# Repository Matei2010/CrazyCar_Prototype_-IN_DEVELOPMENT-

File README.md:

CrazyCar

This is my project for the Crazy Car Competition at FH JOANNEUM in Graz.

The goal is to design and build a small autonomous racing car. The car is supposed to drive around a track on its own using distance sensors and a custom control system.

I made it because i want to win at the Crazy car competition and beacuse i love it to design complicated PCBs.

Full Assembly:

Hardware

The current design includes five VL53L0X time-of-flight distance sensors at the front of the car. Since these sensors use the same I2C address, an I2C multiplexer is included in the design.

For the motors, I am planning to use RZ7889 motor drivers in combination with TMCS1100A3QDR current sensing. The motors are not fully decided yet. Possible options are high-power N20 geared motors or custom geared coreless motors.At the moment i am leaning more towards n20 Motors.

The car is also planned to have a centrifugal fan underneath it to create suction and increase grip. It will generate about 1-1.5 Kg of downforce on the car. 

PCB

The schematic and PCB layout were designed in KiCad. The current design is waiting for approval from my teacher, since this is my first actual complicated PCB, i like to be sure bevore I waiste money on it.

No PCB has been manufactured yet, and no hardware has been assembled or tested. Some component choices and parts of the design may still change.

Front copper:

Back Copper:

3D_Model:

Schematic:

Repository

This repository contains the KiCad project files, including the schematic and PCB layout.

The project is still in the design phase, so things may change as development continues.

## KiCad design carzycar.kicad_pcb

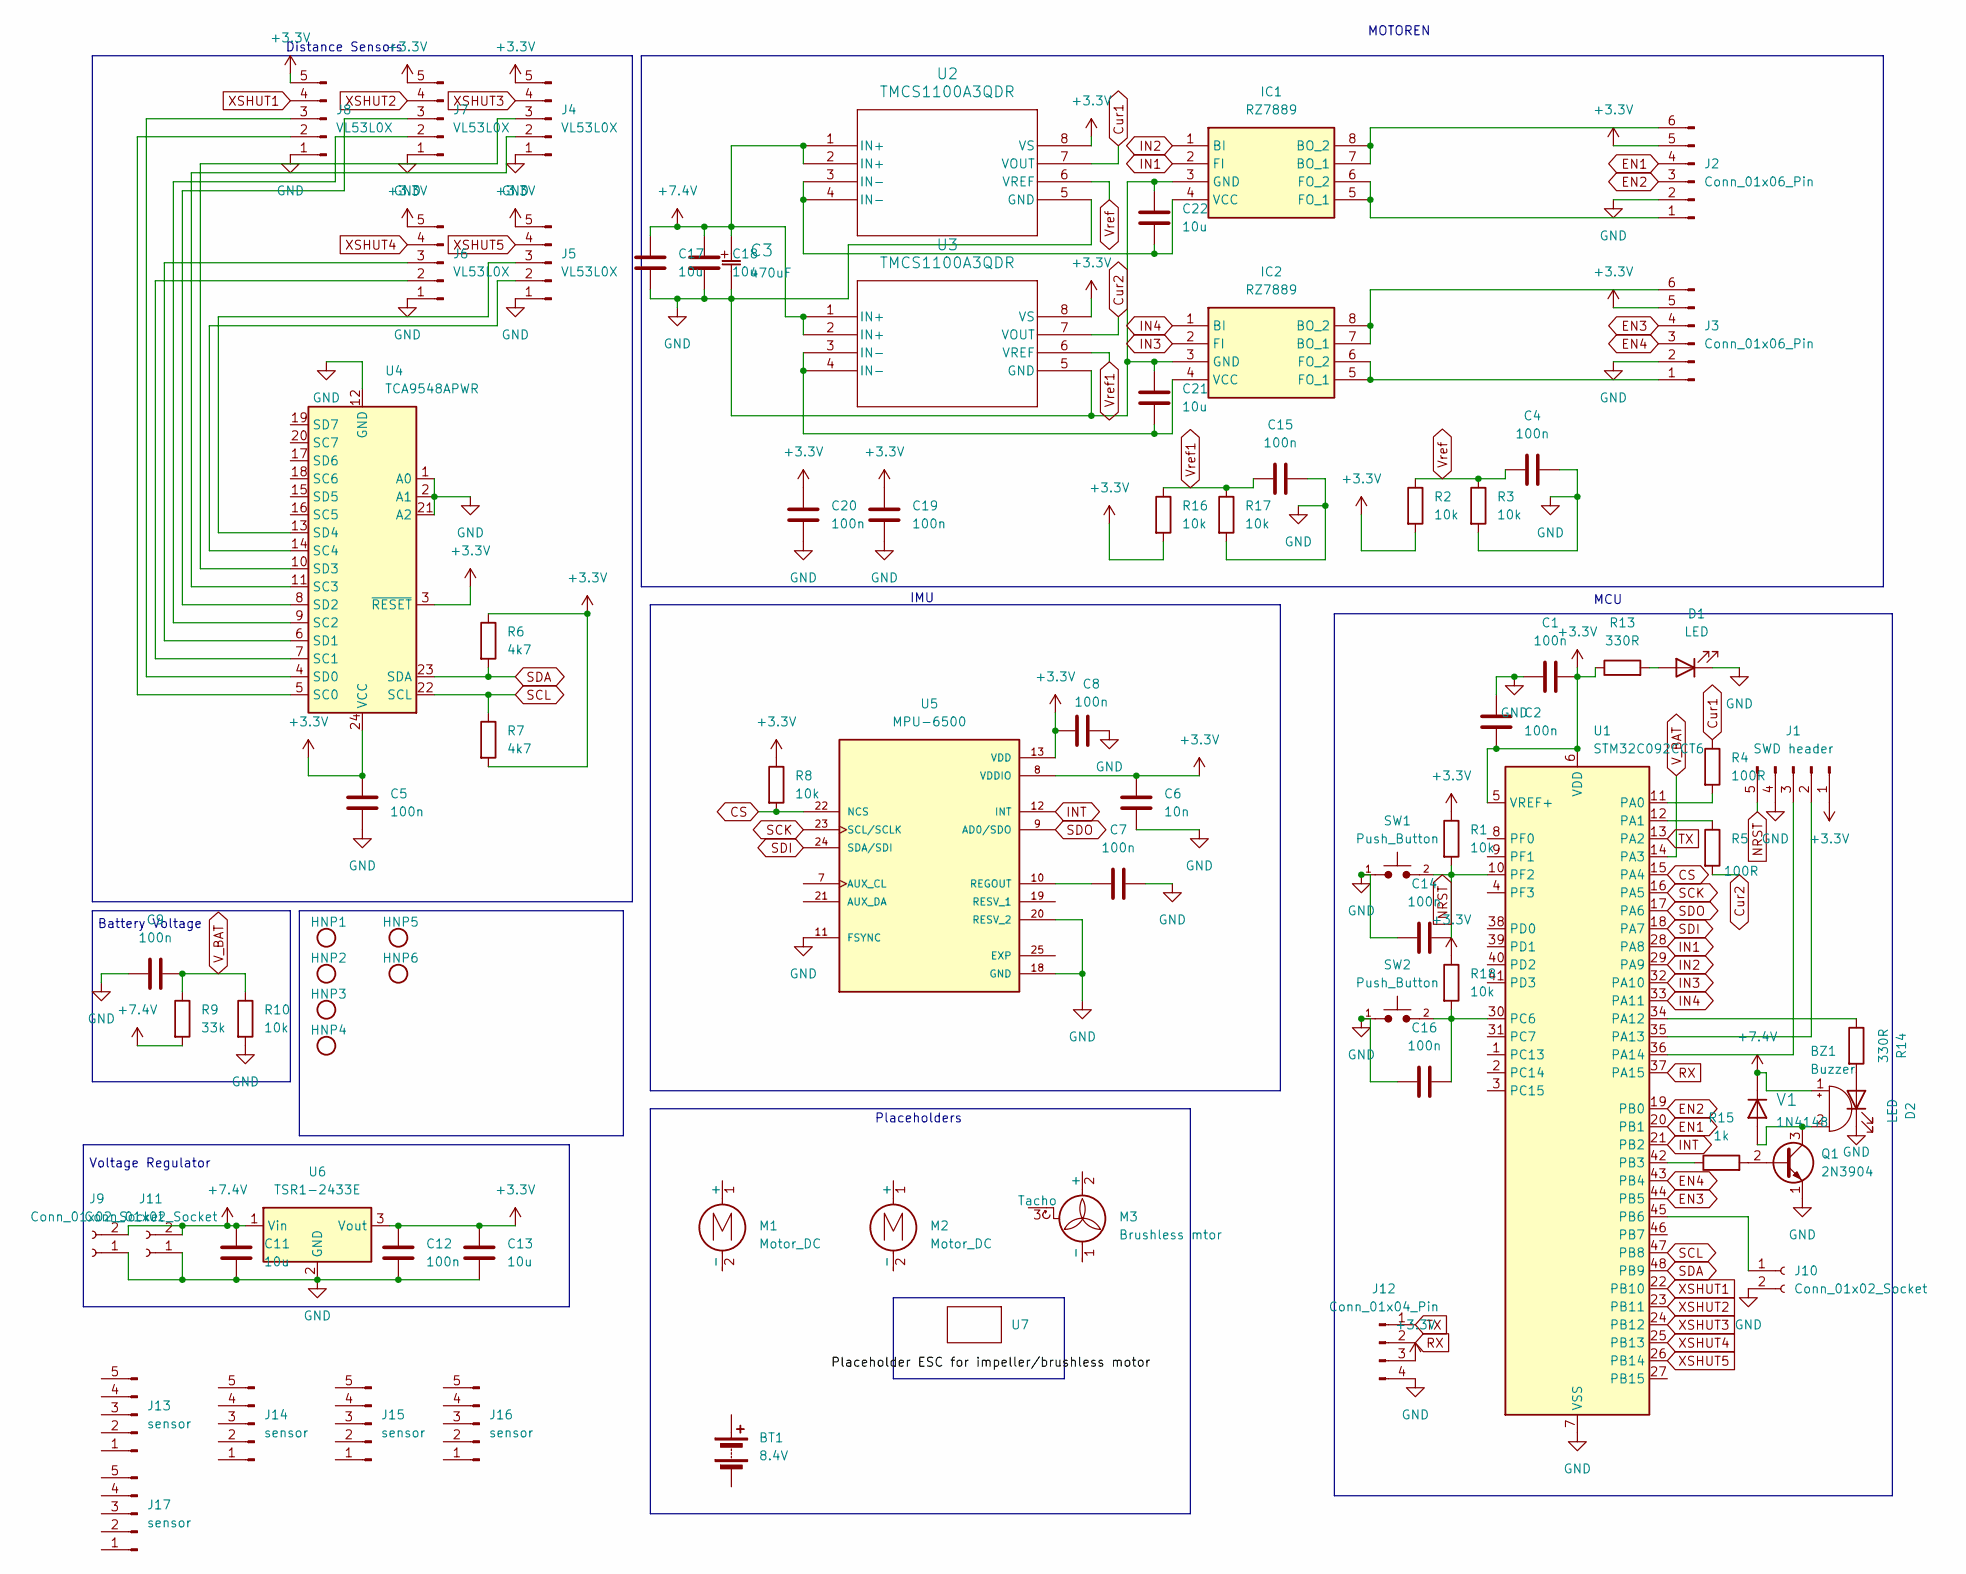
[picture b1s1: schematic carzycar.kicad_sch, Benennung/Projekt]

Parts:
BT1: 8.4V
BZ1: Buzzer; Buzzer_12x9.5RM7.6; PART_NO TMB12A12
C1, C2, C4, C5, C7, C8, C9, C12, C14, C15, C16, C19, C20: 100n; C_0805_2012Metric; PART_NO CC0805KRX7R9BB104
C3: 470uF; CP_Radial_D8.0mm_P3.50mm; PART_NO 03EC0575
C6: 10n; C_0805_2012Metric; PART_NO TCC0805X7R103K500DT
C11, C13, C17, C18, C21, C22: 10u; C_0805_2012Metric; PART_NO GRM21BR61H106KE43L
D1, D2: LED; LED_0805_2012Metric; PART_NO XL-1608SURC-06
HNP1, HNP2, HNP3, HNP4, HNP5, HNP6: NPH; MountingHole_2.2mm_M2
IC1, IC2: RZ7889; SOIC127P600X175-8N; Manufacturer_Part_Number RZ7889
J1: SWD header; PinHeader_1x05_P2.54mm_Vertical; PART_NO B-2100S40P-A110
J2, J3: Conn_01x06_Pin; PinHeader_1x06_P2.54mm_Vertical; PART_NO B-2100S40P-A110
J4, J5, J6, J7, J8: VL53L0X; PinHeader_1x05_P2.54mm_Vertical; PART_NO B-2100S40P-A110
J9, J11: Conn_01x02_Socket; AMASS_XT30U-F_1x02_P5.0mm_Vertical; PART_NO XT30U-F
J10: Conn_01x02_Socket; PinHeader_1x02_P2.54mm_Vertical; PART_NO B-2100S40P-A110
J12: Conn_01x04_Pin; PinHeader_1x04_P2.54mm_Vertical; PART_NO B-2100S40P-A110
J13, J14, J15, J16, J17: sensor
M1, M2: Motor_DC; N20_with_encoder
M3: Brushless mtor
Q1: 2N3904; TO-92_Inline; PART_NO 2N3904BU
R1, R2, R3, R8, R10, R16, R17, R18: 10k; R_0805_2012Metric; PART_NO 0805W8F1002T5E
R4, R5: 100R; R_0805_2012Metric; PART_NO FRC0805F1000TS
R6, R7: 4k7; R_0805_2012Metric; PART_NO FRC0805F4701TS
R9: 33k; R_0805_2012Metric; PART_NO FRC0805F3302TS
R13, R14: 330R; R_0805_2012Metric; PART_NO 0805W8F3300T5E
R15: 1k; R_0805_2012Metric; PART_NO RC0805FR-071KL
SW1, SW2: Push_Button; SW_PUSH_6mm; PART_NO TS-6645DD-6x6x5-100
U1: STM32C092CCT6; LQFP-48_7x7mm_P0.5mm; PART_NO STM32C092CCT6
U2, U3: TMCS1100A3QDR; SOIC8_D_TEX; PART_NO TMCS1100A3QDR
U4: TCA9548APWR; TSSOP-24_4.4x7.8mm_P0.65mm; PART_NO TCA9548APWR
U5: MPU-6500; QFN40P300X300X95-25N; PARTREV 1.3
U6: TSR1-2433E; Converter_DCDC_TRACO_TSR1-xxxxE_THT; PART_NO TSR 1-2433
U7: (no value)
V1: 1N4148; D_DO-35_SOD27_P7.62mm_Horizontal; PART_NO 1N4148

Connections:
+3.3V: C1.2, C2.1, C5.1, C6.1, C8.1, C12.1, C13.1, C19.1, C20.1, J1.1, J2.5, J3.5, J4.5, J5.5, J6.5, J7.5, J8.5, J12.3, R1.1, R2.2, R6.1, R7.2, R8.1, R13.1, R16.2, R18.1, U1.5 (VREF+), U1.6 (VDD), U2.8 (VS), U3.8 (VS), U4.3 (~RESET), U4.24 (VCC), U5.8 (VDDIO), U5.13 (VDD), U6.3 (Vout)
+7.4V: BZ1.1 (+), C3.1 (+), C11.1, C17.1, C18.1, J9.2, J11.2, R9.2, U2.1 (IN+), U2.2 (IN+), U3.1 (IN+), U3.2 (IN+), U6.1 (Vin), V1.1 (C)
CS: R8.2, U1.15 (PA4), U5.22 (NCS)
Cur1: R4.1, U2.7 (VOUT)
Cur2: R5.2, U3.7 (VOUT)
EN1: J2.4, U1.20 (PB1)
EN2: J2.3, U1.19 (PB0)
EN3: J3.4, U1.44 (PB5)
EN4: J3.3, U1.43 (PB4)
GND: C1.1, C2.2, C3.2 (-), C4.2, C5.2, C6.2, C7.2, C8.2, C9.1, C11.2, C12.2, C13.2, C14.1, C15.2, C16.1, C17.2, C18.2, C19.2, C20.2, C21.1, C22.1, D1.1 (K), D2.1 (K), IC1.3 (GND), IC2.3 (GND), J1.4, J2.2, J3.2, J4.1, J5.1, J6.1, J7.1, J8.1, J9.1, J10.2, J11.1, J12.4, Q1.1 (E), R3.2, R10.2, R17.2, SW1.1, SW2.1, U1.7 (VSS), U2.5 (GND), U3.5 (GND), U4.1 (A0), U4.2 (A1), U4.12 (GND), U4.21 (A2), U5.11 (FSYNC), U5.18 (GND), U5.20 (RESV_2), U6.2 (GND)
IN1: IC1.2 (FI), U1.28 (PA8)
IN2: IC1.1 (BI), U1.29 (PA9)
IN3: IC2.2 (FI), U1.32 (PA10)
IN4: IC2.1 (BI), U1.33 (PA11)
INT: U1.21 (PB2), U5.12 (INT)
NRST: C14.2, J1.5, R1.2, SW1.2, U1.10 (PF2)
unnamed: BZ1.2 (-), Q1.3 (C), V1.2 (A)
unnamed: D1.2 (A), R13.2
unnamed: D2.2 (A), R14.2
unnamed: IC1.7 (BO_1), IC1.8 (BO_2), J2.6
unnamed: IC1.5 (FO_1), IC1.6 (FO_2), J2.1
unnamed: C22.2, IC1.4 (VCC), U2.3 (IN-), U2.4 (IN-)
unnamed: IC2.7 (BO_1), IC2.8 (BO_2), J3.6
unnamed: IC2.5 (FO_1), IC2.6 (FO_2), J3.1
unnamed: C21.2, IC2.4 (VCC), U3.3 (IN-), U3.4 (IN-)
unnamed: J1.2, U1.35 (PA13)
unnamed: J1.3, U1.36 (PA14)
unnamed: J4.2, U4.11 (SC3)
unnamed: J4.3, U4.10 (SD3)
unnamed: J5.2, U4.14 (SC4)
unnamed: J5.3, U4.13 (SD4)
unnamed: J6.2, U4.7 (SC1)
unnamed: J6.3, U4.6 (SD1)
unnamed: J7.2, U4.9 (SC2)
unnamed: J7.3, U4.8 (SD2)
unnamed: J8.2, U4.5 (SC0)
unnamed: J8.3, U4.4 (SD0)
unnamed: J10.1, U1.45 (PB6)
unnamed: Q1.2 (B), R15.2
unnamed: R4.2, U1.11 (PA0)
unnamed: R5.1, U1.12 (PA1)
unnamed: R14.1, U1.34 (PA12)
unnamed: R15.1, U1.42 (PB3)
unnamed: C16.2, R18.2, SW2.2, U1.30 (PC6)
unnamed: C7.1, U5.10 (REGOUT)
RX: J12.2, U1.37 (PA15)
SCK: U1.16 (PA5), U5.23 (SCL/SCLK)
SCL: R7.1, U1.47 (PB8), U4.22 (SCL)
SDA: R6.2, U1.48 (PB9), U4.23 (SDA)
SDI: U1.18 (PA7), U5.24 (SDA/SDI)
SDO: U1.17 (PA6), U5.9 (AD0/SDO)
TX: J12.1, U1.13 (PA2)
V_BAT: C9.2, R9.1, R10.1, U1.14 (PA3)
Vref: C4.1, R2.1, R3.1, U2.6 (VREF)
Vref1: C15.1, R16.1, R17.1, U3.6 (VREF)
XSHUT1: J8.4, U1.22 (PB10)
XSHUT2: J7.4, U1.23 (PB11)
XSHUT3: J4.4, U1.24 (PB12)
XSHUT4: J6.4, U1.25 (PB13)
XSHUT5: J5.4, U1.26 (PB14)

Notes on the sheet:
Distance Sensors
Battery Voltage
Voltage Regulator
MOTOREN
Placeholders
IMU
MCU

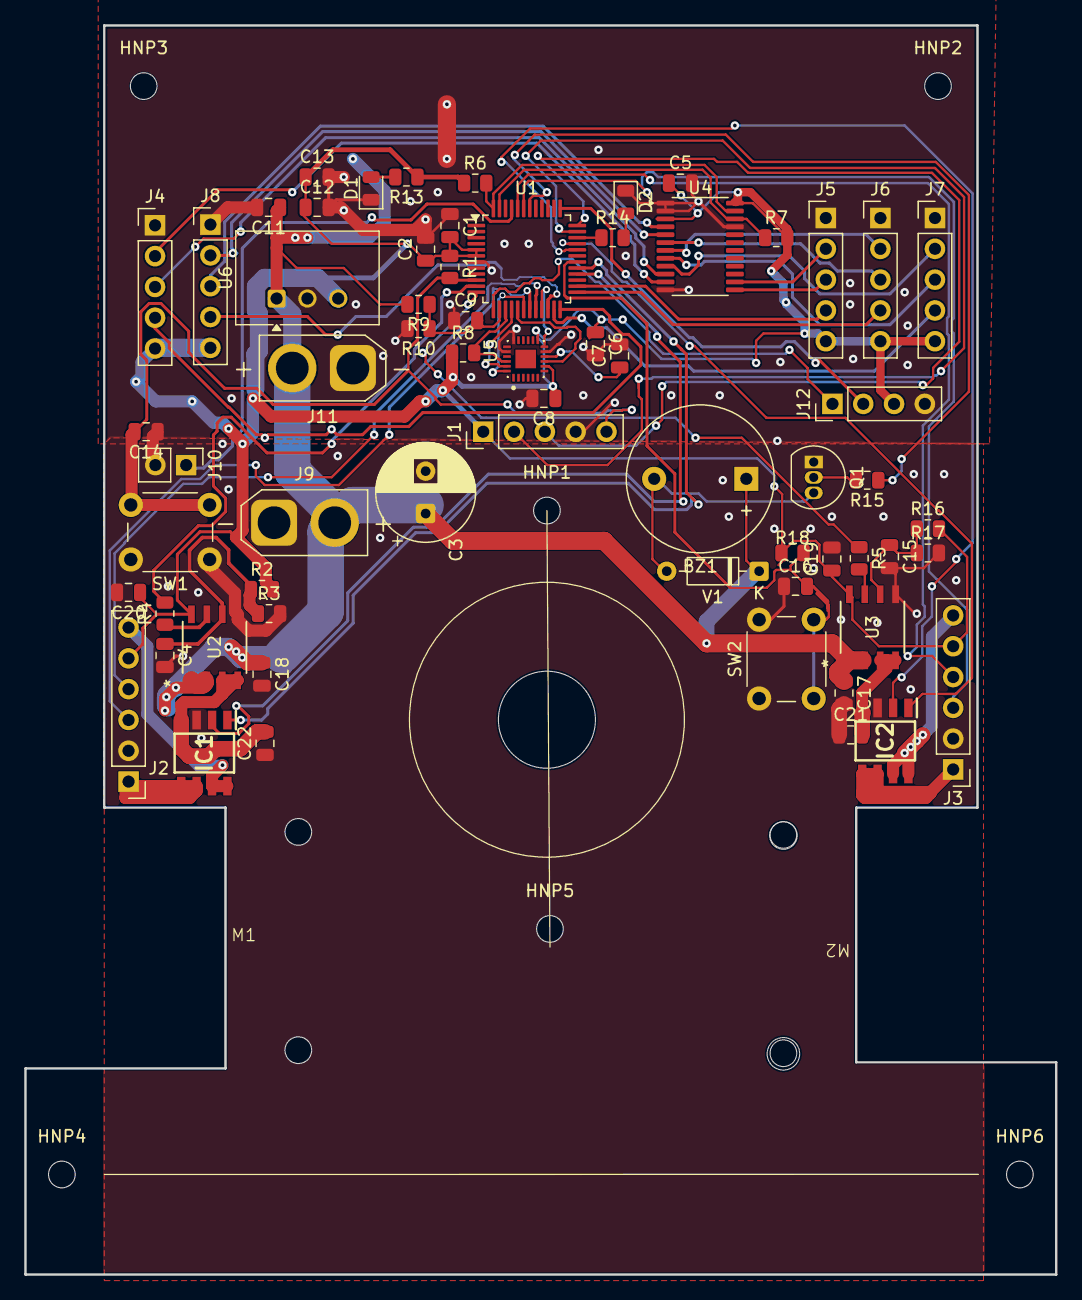
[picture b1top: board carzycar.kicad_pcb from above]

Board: 2 copper layers, 85.0 x 103.0 mm, 72 parts (0 on the bottom side), 60 nets.

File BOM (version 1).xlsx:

Reference | Value | Datasheet | Footprint | Qty | DISTRIBUTOR | MANUFACTURER | ORDER_NO | PART_NO | Beschreibung | PRICE_UNIT | CATEGORY | Full price (exkl Tax and Shipping) | shipping
BT1 | 8.4V |  |  | 1 | Rotorama | CNHL |  | https://www.rotorama.de/product/cnhl-ministar-hv-450mah-2s-70c | CNHL Ministar HV 450mAh 2S 70C | 5.99 |  | 5.99 | LCSC | "=" | 32.14 |  | (Global standard directline is about 20€ cheaper, but Requires a 50€ tarriffhol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
BZ1 | Buzzer |  | Buzzer_Beeper:Buzzer_12x9.5RM7.6 | 5 | LCSC | XHXDZ | C49246932 | TMB12A12 | Buzzer, polarized | 0.18840000000000001 |  | 0.94200000000000006 | Aliexpress | "=" | 12 | Free "Choice Shipping" but i have to pay 12€ in tarrifs to austria
C1,C2,C4,C5,C7,C8,C9,C12,C14,C15,C16,C19,C20 | 100n |  | Capacitor_SMD:C_0805_2012Metric | 20 | LCSC | YAGEO | C49678 | CC0805KRX7R9BB104 | Unpolarized capacitor | 0.19 |  | 3.8 | Rotorama | "=" | 5.58
C3 | 470uF |  | Capacitor_THT:CP_Radial_D8.0mm_P3.50mm | 1 | LCSC | KNSCHA | C2831775 | 03EC0575 |  | 4.1500000000000002E-2 |  | 4.1500000000000002E-2
C6 | 10n |  | Capacitor_SMD:C_0805_2012Metric | 100 | LCSC | CCTC | C282728 | TCC0805X7R103K500DT | Unpolarized capacitor | 6.1000000000000004E-3 |  | 0.61
C11,C13,C17,C18,C21,C22 | 10u |  | Capacitor_SMD:C_0805_2012Metric | 6 | LCSC | muRata | C440198 | GRM21BR61H106KE43L | Unpolarized capacitor | 0.182 |  | 1.0920000000000001
D1,D2 | LED |  | LED_SMD:LED_0805_2012Metric | 100 | LCSC | XINGLIGHT | C965799 | XL-1608SURC-06 | Light emitting diode | 0.01 |  | 1
IC1,IC2 | RZ7889 | http://www.rz-mic.com/uploadfile/fj/2011122615211.pdf | RZ7889:SOIC127P600X175-8N | 2 | LCSC | MSKSEMI | C22462543 | RZ7889-MS | SOP-8 3A Single-CH DC Motor Driver Circuit | 0.43359999999999999 |  | 0.86719999999999997
J1 | SWD header |  | Connector_PinHeader_2.54mm:PinHeader_1x05_P2.54mm_Vertical | 1 | LCSC | Ckmtw | C124377 | B-2100S40P-A110 | Generic connector, single row, 01x05, script generated | 0.25419999999999998 |  | 0.25419999999999998
J2,J3 | Conn_01x06_Pin |  | Connector_PinHeader_2.54mm:PinHeader_1x06_P2.54mm_Vertical | 2 | LCSC | Ckmtw | C124377 | B-2100S40P-A110 | Generic connector, single row, 01x06, script generated | 0.25419999999999998 |  | 0.50839999999999996
J4,J5,J6,J7,J8 | VL53L0X |  | Connector_PinHeader_2.54mm:PinHeader_1x05_P2.54mm_Vertical | 5 | LCSC | Ckmtw | C124377 | B-2100S40P-A110 | Generic connector, single row, 01x05, script generated | 0.25419999999999998 |  | 1.2709999999999999
J9,J11 | Conn_01x02_Socket |  | Connector_AMASS:AMASS_XT30U-F_1x02_P5.0mm_Vertical | 2 | LCSC | AMASS | C99102 | XT30U-F | Generic connector, single row, 01x02, script generated | 0.192 |  | 0.38400000000000001
J10 | Conn_01x02_Socket |  | Connector_PinHeader_2.54mm:PinHeader_1x02_P2.54mm_Vertical | 1 | LCSC | Ckmtw | C124377 | B-2100S40P-A110 | Generic connector, single row, 01x02, script generated | 0.25419999999999998 |  | 0.25419999999999998
J12 | Conn_01x04_Pin |  | Connector_PinHeader_2.54mm:PinHeader_1x04_P2.54mm_Vertical | 1 | LCSC | Ckmtw | C124377 | B-2100S40P-A110 | Generic connector, single row, 01x04, script generated | 0.25419999999999998 |  | 0.25419999999999998
J13,J14,J15,J16,J17 | sensor |  |  | 5 |  | Sailstart | https://de.aliexpress.com/item/1005007639367196.html?spm=a2g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 |  | Cheapest Aliexpress Vl53L0x sensors | 2 |  | 10
M1,M2 | Motor_DC |  | minimouse:N20_with_encoder | 2 |  |  | https://de.aliexpress.com/item/1005007886406269.html?spm=a2g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 |  | DC Motor | 6.85 |  | 13.7
M3 | Brushless mtor |  |  | 1 | Rotorama |  | https://www.rotorama.de/product/happymodel-rs0802-20000kv-2 |  | Happymodel RS0802 20000Kv Brushless mtor | 9.99 |  | 9.99
Q1 | 2N3904 | https://www.onsemi.com/pub/Collateral/2N3903-D.PDF | Package_TO_SOT_THT:TO-92_Inline | 5 | LCSC | onsemi | C124482 | 2N3904BU | 0.2A Ic, 40V Vce, Small Signal NPN Transistor, TO-92 | 9.4500000000000001E-2 |  | 0.47250000000000003
R1,R2,R3,R8,R10,R16,R17,R18 | 10k |  | Resistor_SMD:R_0805_2012Metric | 100 | LCSC | UNI-ROYAL | C17414 | 0805W8F1002T5E | Resistor | 3.2000000000000002E-3 |  | 0.32
R4,R5 | 100R |  | Resistor_SMD:R_0805_2012Metric | 100 | LCSC | FOJAN | C2907218 | FRC0805F1000TS | Resistor | 2.8999999999999998E-3 |  | 0.28999999999999998
R6,R7 | 4k7 |  | Resistor_SMD:R_0805_2012Metric | 100 | LCSC | FOJAN | C2907264 | FRC0805F4701TS | Resistor | 2.5999999999999999E-3 |  | 0.26
R9 | 33k |  | Resistor_SMD:R_0805_2012Metric | 100 | LCSC | FOJAN | C2933415 | FRC0805F3302TS | Resistor | 2.8E-3 |  | 0.27999999999999997
R13,R14 | 330R |  | Resistor_SMD:R_0805_2012Metric | 100 | LCSC | UNI-ROYAL | C17630 | 0805W8F3300T5E | Resistor | 4.1999999999999997E-3 |  | 0.42 |  |  |  | FULL PRICE:
R15 | 1k |  | Resistor_SMD:R_0805_2012Metric | 100 | LCSC | YAGEO | C95781 | RC0805FR-071KL | Resistor | 2.8999999999999998E-3 |  | 0.28999999999999998 |  |  |  | 109.11
SW1,SW2 | Push_Button |  | Button_Switch_THT:SW_PUSH_6mm | 10 | LCSC | CAX | C53431127 | TS-6645DD-6x6x5-100 | Common 6mmx6mm Push Button | 3.61E-2 |  | 0.36099999999999999 |  |  |  | (a 20€ buffer would be nice if allowed for surprise customs and duties or if) s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
U1 | STM32C092CCT6 | https://www.st.com/resource/en/datasheet/stm32c092cct6.pdf | Package_QFP:LQFP-48_7x7mm_P0.5mm | 1 | LCSC | ST | C45338511 | STM32C092CCT6 |  | 3.99 |  | 3.99
U2,U3 | TMCS1100A3QDR | https://www.ti.com/lit/gpn/tmcs1100 | TMCS1100A1:SOIC8_D_TEX | 2 | LCSC | TI | C2873352 | TMCS1100A3QDR |  | 2.57 |  | 5.14
U4 | TCA9548APWR | http://www.ti.com/lit/ds/symlink/tca9548a.pdf | Package_SO:TSSOP-24_4.4x7.8mm_P0.65mm | 1 | LCSC | TI | C130026 | TCA9548APWR | Low voltage 8-channel I2C switch with reset, TSSOP-24 | 0.7641 |  | 0.7641
U5 | MPU-6500 |  | MPU-6500:QFN40P300X300X95-25N | 1 | LCSC | TDK InvenSense | C50278 | MPU-6500 | MotionTracking Device Digital Output 1.8V 24-Pin QFN EP T/R | 4.9482999999999997 |  | 4.9482999999999997
U6 | TSR1-2433E | https://www.tracopower.com/products/tsr1e.pdf | Converter_DCDC:Converter_DCDC_TRACO_TSR1-xxxxE_THT | 1 | LCSC | YLPTEC | C53183919 | TSR 1-2433 | 1A step-down regulator, fixed 3.3V output voltage, 6-36V input voltage, TO-220 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 | 3.55 |  | 3.55
U7 |  |  |  | 1 | Rotorama | Graupner |  | https://www.rotorama.de/product/graupner-ultra-control-10a-1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 | Graupner Ultra Control 10A 1-2S BLS | 3.99 |  | 3.99
V1 | 1N4148 | https://diotec.com/request/datasheet/1n4148.pdf | Diode_THT:D_DO-35_SOD27_P7.62mm_Horizontal | 20 | LCSC | onsemi | C258182 | 1N4148 | Kleinsignal Schaltdiode, THT Do-35 (SOD-27), 1N4148, 1N4150, 1N4151, 1N4448 | 2.7199999999999998E-2 |  | 0.54399999999999993
 |  |  |  |  |  |  |  |  |  |  |  | 76.57859999999998
